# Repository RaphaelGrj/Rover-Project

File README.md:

# Rover-Project (Not Available - In development)
Coming soon

🤖 PROJECT ROVER | by R-Bot

L'évolution mobile de LUMI. 
Un compagnon robotique autonome, intelligent, et intégré à l'écosystème domotique, arborant la signature esthétique "Glitch" de R-Bot.

📖 Présentation du Projet 

Project Rover est le successeur spirituel de LUMI. Là où LUMI observait depuis son bureau, Rover explore. Fortement inspiré par la mécanique et l'expressivité du robot Vector (Anki), Rover va plus loin en devenant un véritable assistant domotique mobile.

Il ne s'agit pas d'un simple jouet télécommandé, mais d'une machine à émotions capable d'interagir naturellement avec son environnement et son humain. Conçu autour d'une architecture hybride (ESP32 WROOM embarqué + Raspberry Pi déporté sur le réseau), Rover surveille le logement, analyse l'air, interagit via une IA générative, et patrouille tout en gardant une direction artistique unique : un design "Vector Glitché".

🎯 Cahier des Charges & Fonctionnalités

  🧠 Machine à Émotions & IA
Personnalité Dynamique : Humeurs variables selon le contexte (météo, niveau de batterie, interactions récentes).
Expressivité Physique : Affichage d'animations sur écran IPS (yeux type Vector) combiné à des mouvements de tête fluides (Pitch/Yaw) gérés par servomoteurs.
Cerveau IA : Intégration d'une IA conversationnelle pour répondre aux requêtes de manière naturelle (évolution du système embarqué sur LUMI).
Mise en place d’un systeme de mise a jour OTA

  🛞 Mobilité & NavigationDéplacement Autonome : 
  Exploration libre du logement avec évitement d'obstacles.
  Pilotage Manuel : Prise de contrôle à distance via smartphone ou télécommande (avec retour vidéo direct).
  
  -[À l'étude] Cartographie & Patrouille : Algorithme SLAM pour générer une carte de la maison, avec des rondes de sécurité programmables.-
  -[À l'étude] Visualisation en réalité augmentée : la carte (et un premier HUD de télémétrie déjà en place) consultable en direct dans un casque compatible WebXR (ex. Meta Quest 3), en superposition sur la vraie pièce -- voir ARCHITECTURE_AND_ROADMAP.md §13.1.-
  
  👁️ Perception & VisionReconnaissance Visuelle : 
  Capacité à identifier son humain (reconnaissance faciale), à détecter des objets, des présences inconnues, ou même des animaux (idéal pour surveiller si votre compagnon fait des bêtises en votre absence).
  Surveillance Distante : Flux caméra accessible hors du domicile pour lever le doute lors d'une alerte.
  
  🏠 Hub Domotique & Capteurs (Home Assistant)
  Lien Home Assistant : Intégration native via MQTT/API. Rover peut déclencher des scènes ou annoncer des notifications de la maison.Bilan Météo Local : Station météo sur chenilles. 
  Analyse en temps réel de la température, de l'humidité et de la pression.
  -[À l'étude] Sécurité Environnementale : Détection de COV (Composés Organiques Volatils), de fumée et de qualité de l'air. Rover alerte en cas de risque d'incendie ou de dégradation de l'air intérieur.-
  
  🎨 Direction Artistique (DA)Design R-Bot "Glitch" : 
  Esthétique asymétrique, textures corrompues ou détails cyberpunk. Modélisation complète sous SolidWorks, optimisée pour un assemblage mêlant l'endurance du FDM (châssis) et la précision de la résine (coque/visage).
  
  ⚙️ Architecture Matérielle (BOM - Bill of Materials)
L'architecture est divisée en deux couches pour garantir fluidité et puissance de calcul.

### Cerveaux & Logique

| Composant | Rôle |
| :--- | :--- |
| **ESP32 WROOM** | *(embarqué)* Microcontrôleur temps réel : gestion des moteurs, servos, capteurs I2C et écran SPI. |
| **ESP32-CAM** | *(embarqué)* Module caméra indépendant, sert son flux MJPEG sur le réseau local. |
| **Raspberry Pi 3B+** | *(**déporté sur le réseau** depuis le 2026-09-15)* Serveur vidéo, traitement IA lourde, SLAM, lien Home Assistant. |

> **Le Raspberry Pi n'est plus embarqué sur le robot.** Il vit sur le
> réseau local et dialogue avec l'ESP32 par une socket TCP WiFi
> (Rover Protocol inchangé). Le châssis ne porte plus qu'ESP32 +
> ESP32-CAM + batterie --- gain d'encombrement et d'autonomie, et « le
> cerveau » peut désormais être n'importe quelle machine du LAN, pas
> forcément un Pi. Raisonnement complet :
> `ARCHITECTURE_AND_ROADMAP.md` §6.2.

### Locomotion & Mouvement

| Composant | Rôle |
| :--- | :--- |
| **2x Moteurs DC N20 (avec encodeurs)** | Propulsion précise des chenilles ou roues. |
| **1x Driver Moteur (DRV8833)** | Contrôle de puissance des moteurs. |
| **2x Micro Servomoteurs (SG90 ou MG90S)** | Mouvement de la tête (Axe X et Y) pour l'expressivité. |

### Perception & Capteurs

| Composant | Rôle |
| :--- | :--- |
| **Module Caméra (Pi Camera V2 ou OV2640)** | Vision, reconnaissance faciale, retour vidéo. |
| **MPU6050 (IMU)** | Accéléromètre & Gyroscope (équilibre, détection de chute ou si on le soulève). |
| **Capteur ToF (VL53L0X) x2** | Mesure de distance laser précise (évitement d'obstacles sans contact). |
| **BME688 (Bosch)** | Capteur 4-en-1 : Température, Humidité, Pression barométrique et Gaz/COV (idéal pour le bilan météo et risque incendie). |

### Interface Humain-Machine (IHM)

| Composant | Rôle |
| :--- | :--- |
| **Écran IPS (ex: ST7789 1.54")** | Affichage des yeux, des animations de glitch et des humeurs. |
| **Micro I2S (INMP441)** | Écoute de l'environnement et des commandes vocales. |
| **Ampli Audio (MAX98357A) + Haut-parleur** | Synthèse vocale et bruitages émotionnels. |

### Énergie

| Composant | Rôle |
| :--- | :--- |
| **2x Accus 18650 (Li-ion)** | Autonomie énergétique. |
| **Module BMS / TP4056 + Step-down (LM2596)** | Charge sécurisée et régulation 5V/3.3V pour alimenter l'ESP et le Pi. |

🚀 Roadmap du Développement (Prévisions)

[ ] Phase 1 : Preuve de concept (Châssis & Écran)

Conception SolidWorks de la base roulante.

Test de motorisation avec l'ESP32.

Portage des animations d'yeux depuis le projet LUMI.

[ ] Phase 2 : Architecture Hybride

Communication série/I2C entre le Pi Zero et l'ESP32-S3.

Intégration du flux vidéo et pilotage distant.

[ ] Phase 3 : Écosystème & IA

Connexion à Home Assistant.

Câblage et programmation des capteurs environnementaux (BME688).

Implémentation du modèle IA conversationnel.

[ ] Phase 4 : Les fonctions "À l'étude"

Déploiement d'un nœud ROS ou OpenCV pour le mode patrouille et le mapping.

Reconnaissance faciale et animale en local.

Projet développé par R-Bot. "Glitch the system, but make it cute."

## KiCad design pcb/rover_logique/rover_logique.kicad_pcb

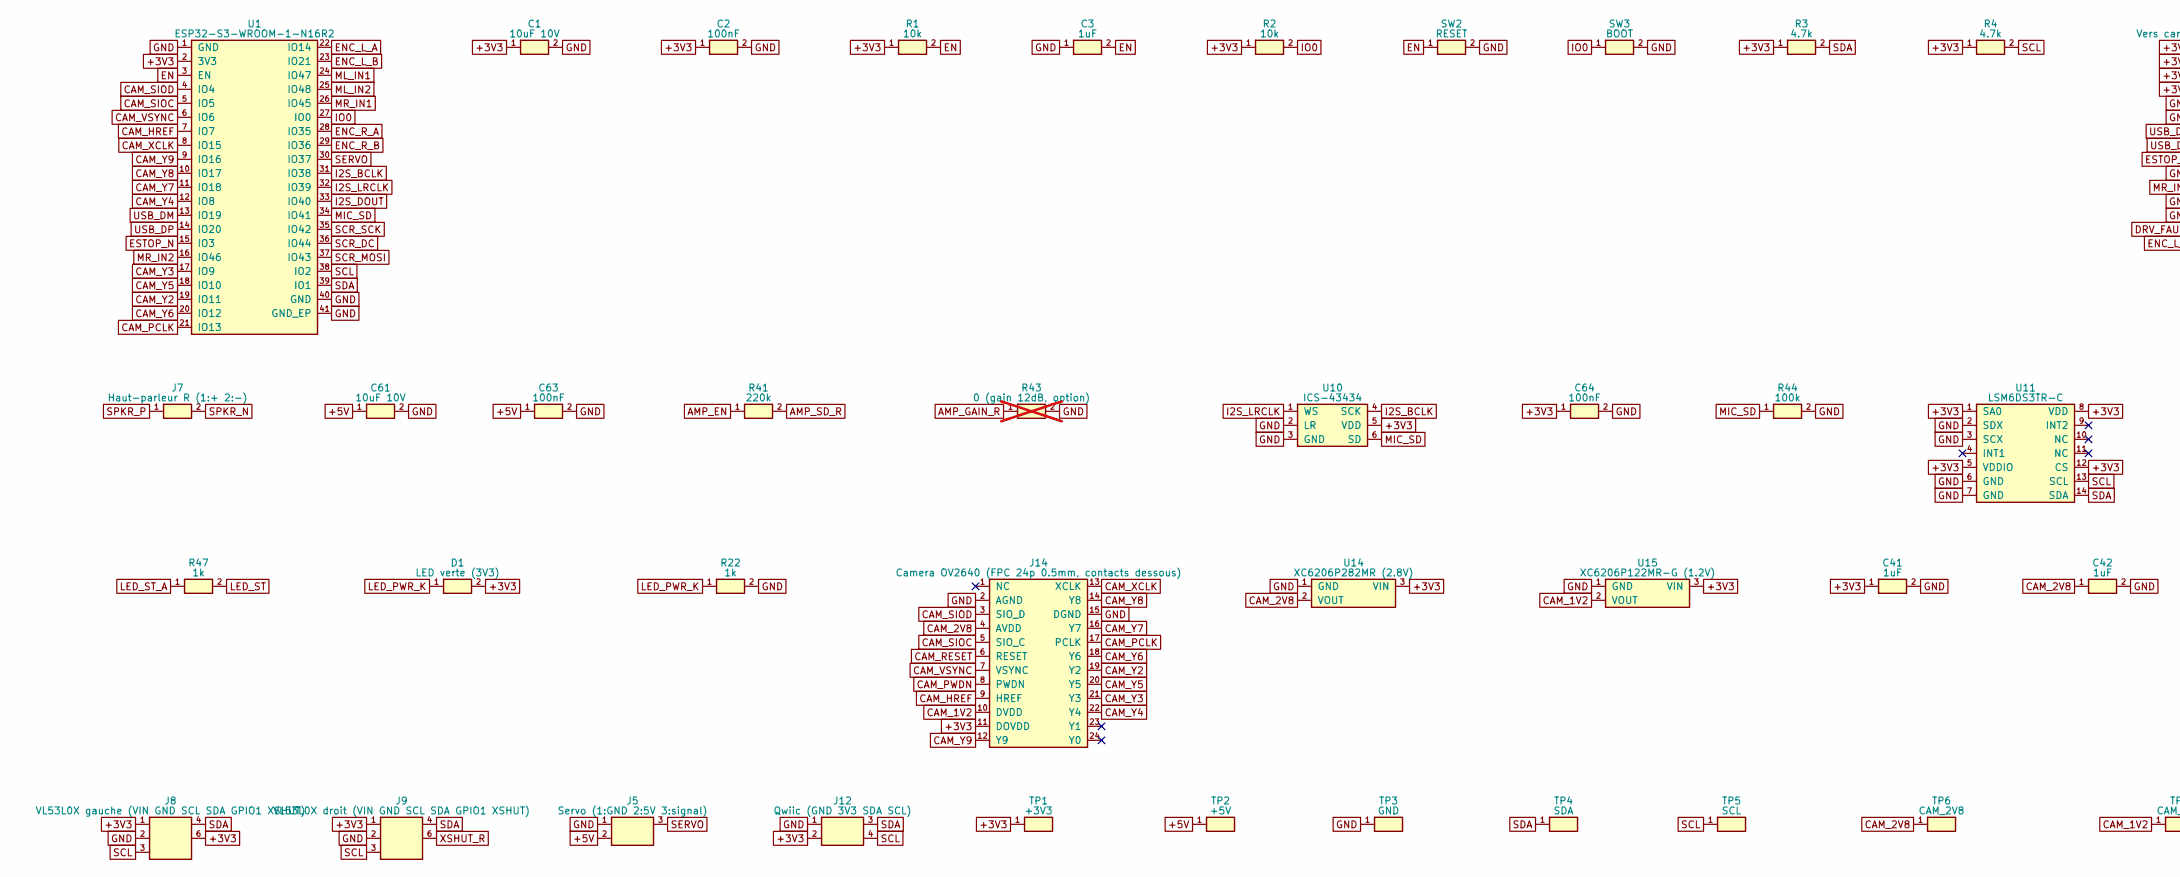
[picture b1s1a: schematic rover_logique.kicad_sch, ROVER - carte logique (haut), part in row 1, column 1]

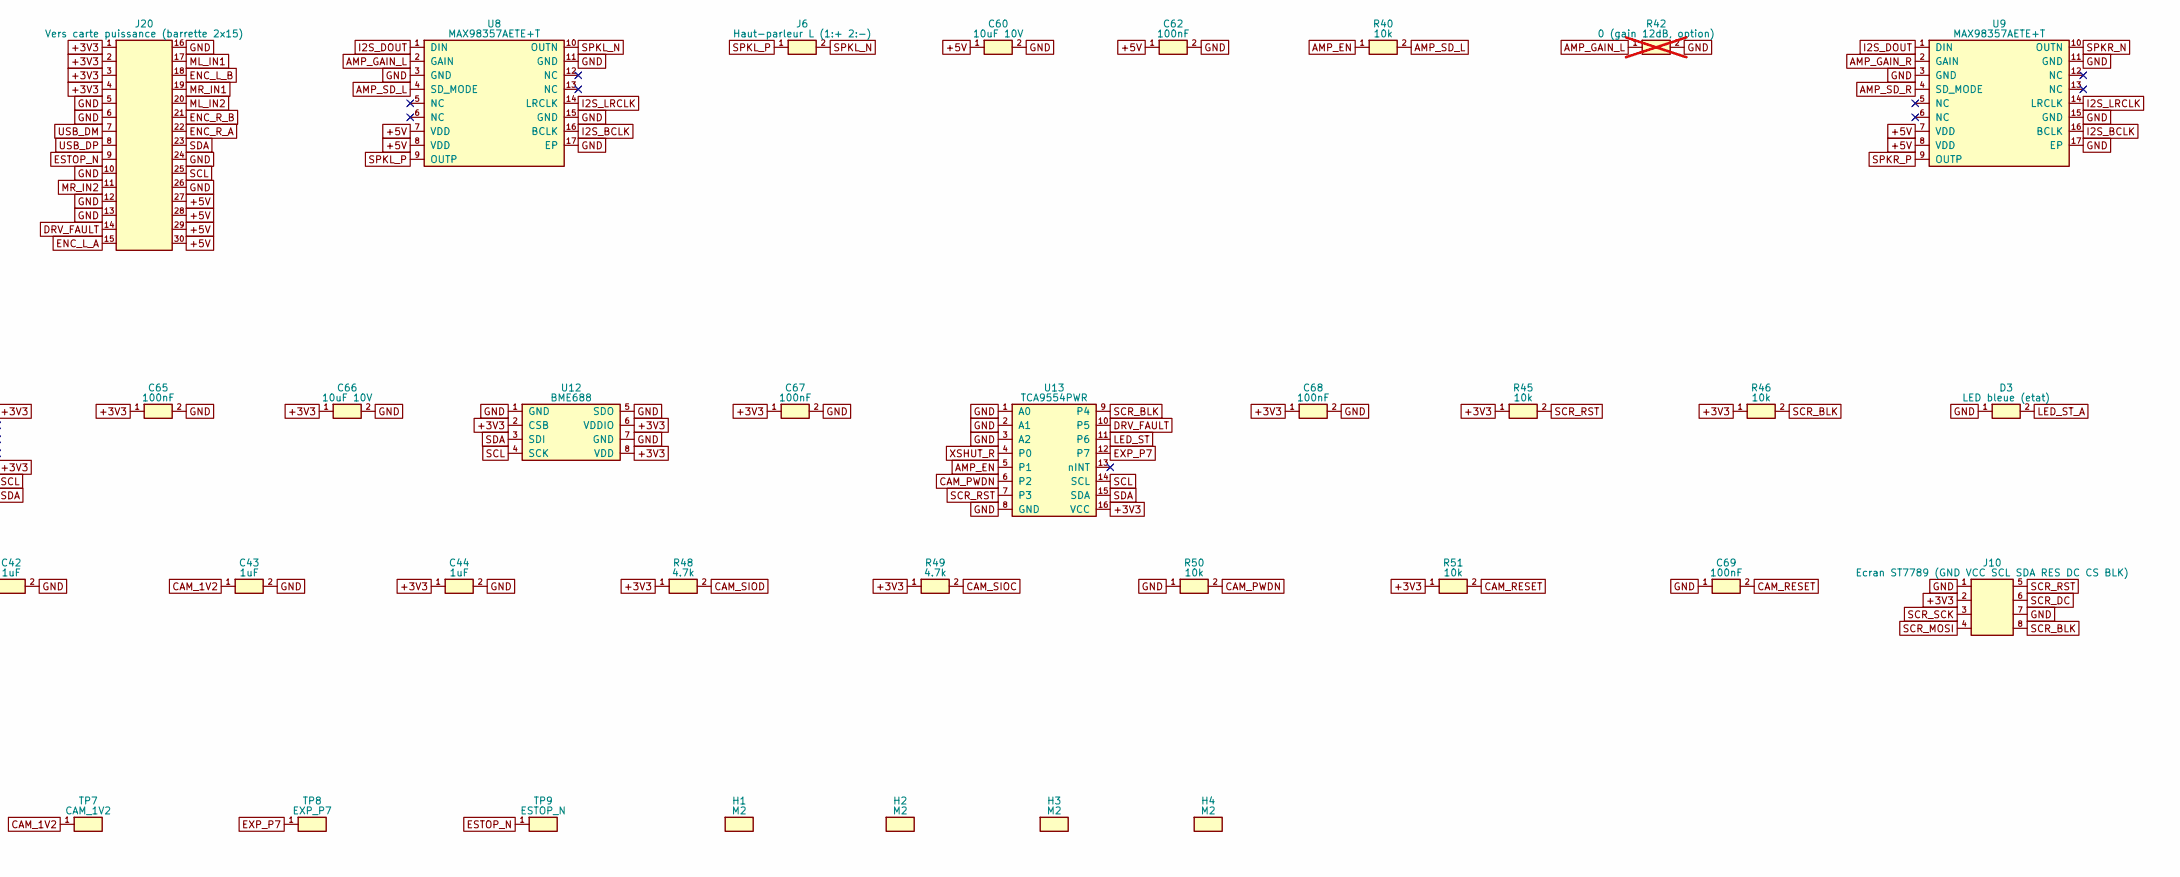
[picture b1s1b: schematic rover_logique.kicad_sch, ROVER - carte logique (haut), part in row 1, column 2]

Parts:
C1, C60, C61, C66: 10uF 10V; C_0805_2012Metric
C2, C62, C63, C64, C65, C67, C68, C69: 100nF; C_0402_1005Metric
C3, C41, C42, C43, C44: 1uF; C_0603_1608Metric
D1: LED verte (3V3); LED_0603_1608Metric
D3: LED bleue (etat); LED_0603_1608Metric
H1, H2, H3, H4: M2; MountingHole_2.2mm_M2
J5: Servo (1:GND 2:5V 3:signal); PinHeader_1x03_P2.54mm_Vertical
J6: Haut-parleur L (1:+ 2:-); JST_PH_S2B-PH-SM4-TB_1x02-1MP_P2.00mm_Horizontal
J7: Haut-parleur R (1:+ 2:-); JST_PH_S2B-PH-SM4-TB_1x02-1MP_P2.00mm_Horizontal
J8: VL53L0X gauche (VIN GND SCL SDA GPIO1 XSHUT); JST_PH_S6B-PH-SM4-TB_1x06-1MP_P2.00mm_Horizontal
J9: VL53L0X droit (VIN GND SCL SDA GPIO1 XSHUT); JST_PH_S6B-PH-SM4-TB_1x06-1MP_P2.00mm_Horizontal
J10: Ecran ST7789 (GND VCC SCL SDA RES DC CS BLK); JST_PH_S8B-PH-SM4-TB_1x08-1MP_P2.00mm_Horizontal
J12: Qwiic (GND 3V3 SDA SCL); JST_SH_SM04B-SRSS-TB_1x04-1MP_P1.00mm_Horizontal
J14: Camera OV2640 (FPC 24p 0.5mm, contacts dessous); Hirose_FH12-24S-0.5SH_1x24-1MP_P0.50mm_Horizontal
J20: Vers carte puissance (barrette 2x15); PinHeader_2x15_P2.54mm_Vertical
R1, R2, R40, R45, R46, R50, R51: 10k; R_0402_1005Metric
R3, R4, R48, R49: 4.7k; R_0402_1005Metric
R22, R47: 1k; R_0402_1005Metric
R41: 220k; R_0402_1005Metric
R42, R43: 0 (gain 12dB, option); R_0402_1005Metric; not fitted
R44: 100k; R_0402_1005Metric
SW2: RESET; SW_Push_1P1T_NO_CK_KMR2
SW3: BOOT; SW_Push_1P1T_NO_CK_KMR2
TP1: +3V3; TestPoint_Pad_D1.0mm
TP2: +5V; TestPoint_Pad_D1.0mm
TP3: GND; TestPoint_Pad_D1.0mm
TP4: SDA; TestPoint_Pad_D1.0mm
TP5: SCL; TestPoint_Pad_D1.0mm
TP6: CAM_2V8; TestPoint_Pad_D1.0mm
TP7: CAM_1V2; TestPoint_Pad_D1.0mm
TP8: EXP_P7; TestPoint_Pad_D1.0mm
TP9: ESTOP_N; TestPoint_Pad_D1.0mm
U1: ESP32-S3-WROOM-1-N16R2; ESP32-S3-WROOM-1_bord
U8, U9: MAX98357AETE+T; TQFN-16-1EP_3x3mm_P0.5mm_EP1.23x1.23mm
U10: ICS-43434; InvenSense_ICS-43434-6_3.5x2.65mm
U11: LSM6DS3TR-C; LGA-14_3x2.5mm_P0.5mm_LayoutBorder3x4y
U12: BME688; Bosch_LGA-8_3x3mm_P0.8mm_ClockwisePinNumbering
U13: TCA9554PWR; TSSOP-16_4.4x5mm_P0.65mm
U14: XC6206P282MR (2.8V); SOT-23
U15: XC6206P122MR-G (1.2V); SOT-23

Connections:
+3V3: C1.1, C2.1, C41.1, C44.1, C64.1, C65.1, C66.1, C67.1, C68.1, D1.2, J8.1, J8.6, J9.1, J10.2, J12.2, J14.11 (DOVDD), J20.1, J20.2, J20.3, J20.4, R1.1, R2.1, R3.1, R4.1, R45.1, R46.1, R48.1, R49.1, R51.1, TP1.1, U1.2 (3V3), U10.5 (VDD), U11.1 (SA0), U11.5 (VDDIO), U11.8 (VDD), U11.12 (CS), U12.2 (CSB), U12.6 (VDDIO), U12.8 (VDD), U13.16 (VCC), U14.3 (VIN), U15.3 (VIN)
+5V: C60.1, C61.1, C62.1, C63.1, J5.2, J20.27, J20.28, J20.29, J20.30, TP2.1, U8.7 (VDD), U8.8 (VDD), U9.7 (VDD), U9.8 (VDD)
AMP_EN: R40.1, R41.1, U13.5 (P1)
AMP_GAIN_L: R42.1, U8.2 (GAIN)
AMP_GAIN_R: R43.1, U9.2 (GAIN)
AMP_SD_L: R40.2, U8.4 (SD_MODE)
AMP_SD_R: R41.2, U9.4 (SD_MODE)
CAM_1V2: C43.1, J14.10 (DVDD), TP7.1, U15.2 (VOUT)
CAM_2V8: C42.1, J14.4 (AVDD), TP6.1, U14.2 (VOUT)
CAM_HREF: J14.9 (HREF), U1.7 (IO7)
CAM_PCLK: J14.17 (PCLK), U1.21 (IO13)
CAM_PWDN: J14.8 (PWDN), R50.2, U13.6 (P2)
CAM_RESET: C69.2, J14.6 (RESET), R51.2
CAM_SIOC: J14.5 (SIO_C), R49.2, U1.5 (IO5)
CAM_SIOD: J14.3 (SIO_D), R48.2, U1.4 (IO4)
CAM_VSYNC: J14.7 (VSYNC), U1.6 (IO6)
CAM_XCLK: J14.13 (XCLK), U1.8 (IO15)
CAM_Y2: J14.19 (Y2), U1.19 (IO11)
CAM_Y3: J14.21 (Y3), U1.17 (IO9)
CAM_Y4: J14.22 (Y4), U1.12 (IO8)
CAM_Y5: J14.20 (Y5), U1.18 (IO10)
CAM_Y6: J14.18 (Y6), U1.20 (IO12)
CAM_Y7: J14.16 (Y7), U1.11 (IO18)
CAM_Y8: J14.14 (Y8), U1.10 (IO17)
CAM_Y9: J14.12 (Y9), U1.9 (IO16)
DRV_FAULT: J20.14, U13.10 (P5)
EN: C3.2, R1.2, SW2.1, U1.3 (EN)
ENC_L_A: J20.15, U1.22 (IO14)
ENC_L_B: J20.18, U1.23 (IO21)
ENC_R_A: J20.22, U1.28 (IO35)
ENC_R_B: J20.21, U1.29 (IO36)
ESTOP_N: J20.9, TP9.1, U1.15 (IO3)
EXP_P7: TP8.1, U13.12 (P7)
GND: C1.2, C2.2, C3.1, C41.2, C42.2, C43.2, C44.2, C60.2, C61.2, C62.2, C63.2, C64.2, C65.2, C66.2, C67.2, C68.2, C69.1, D3.1, J5.1, J8.2, J9.2, J10.1, J10.7, J12.1, J14.2 (AGND), J14.15 (DGND), J20.5, J20.6, J20.10, J20.12, J20.13, J20.16, J20.24, J20.26, R22.2, R42.2, R43.2, R44.2, R50.1, SW2.2, SW3.2, TP3.1, U1.1 (GND), U1.40 (GND), U1.41 (GND_EP), U8.3 (GND), U8.11 (GND), U8.15 (GND), U8.17 (EP), U9.3 (GND), U9.11 (GND), U9.15 (GND), U9.17 (EP), U10.2 (LR), U10.3 (GND), U11.2 (SDX), U11.3 (SCX), U11.6 (GND), U11.7 (GND), U12.1 (GND), U12.5 (SDO), U12.7 (GND), U13.1 (A0), U13.2 (A1), U13.3 (A2), U13.8 (GND), U14.1 (GND), U15.1 (GND)
I2S_BCLK: U1.31 (IO38), U8.16 (BCLK), U9.16 (BCLK), U10.4 (SCK)
I2S_DOUT: U1.33 (IO40), U8.1 (DIN), U9.1 (DIN)
I2S_LRCLK: U1.32 (IO39), U8.14 (LRCLK), U9.14 (LRCLK), U10.1 (WS)
IO0: R2.2, SW3.1, U1.27 (IO0)
LED_PWR_K: D1.1, R22.1
LED_ST: R47.2, U13.11 (P6)
LED_ST_A: D3.2, R47.1
MIC_SD: R44.1, U1.34 (IO41), U10.6 (SD)
ML_IN1: J20.17, U1.24 (IO47)
ML_IN2: J20.20, U1.25 (IO48)
MR_IN1: J20.19, U1.26 (IO45)
MR_IN2: J20.11, U1.16 (IO46)
SCL: J8.3, J9.3, J12.4, J20.25, R4.2, TP5.1, U1.38 (IO2), U11.13 (SCL), U12.4 (SCK), U13.14 (SCL)
SCR_BLK: J10.8, R46.2, U13.9 (P4)
SCR_DC: J10.6, U1.36 (IO44)
SCR_MOSI: J10.4, U1.37 (IO43)
SCR_RST: J10.5, R45.2, U13.7 (P3)
SCR_SCK: J10.3, U1.35 (IO42)
SDA: J8.4, J9.4, J12.3, J20.23, R3.2, TP4.1, U1.39 (IO1), U11.14 (SDA), U12.3 (SDI), U13.15 (SDA)
SERVO: J5.3, U1.30 (IO37)
SPKL_N: J6.2, U8.10 (OUTN)
SPKL_P: J6.1, U8.9 (OUTP)
SPKR_N: J7.2, U9.10 (OUTN)
SPKR_P: J7.1, U9.9 (OUTP)
USB_DM: J20.7, U1.13 (IO19)
USB_DP: J20.8, U1.14 (IO20)
XSHUT_R: J9.6, U13.4 (P0)

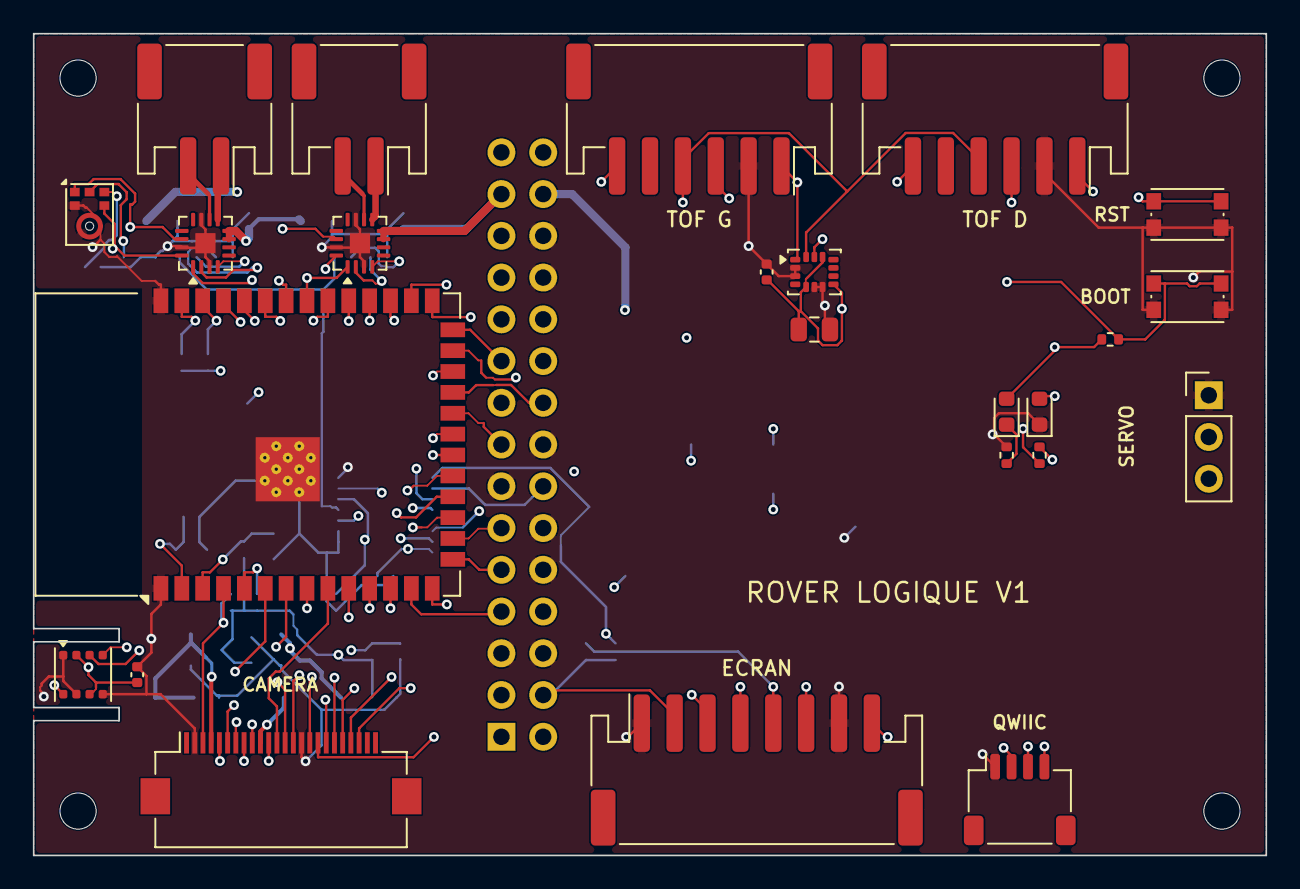
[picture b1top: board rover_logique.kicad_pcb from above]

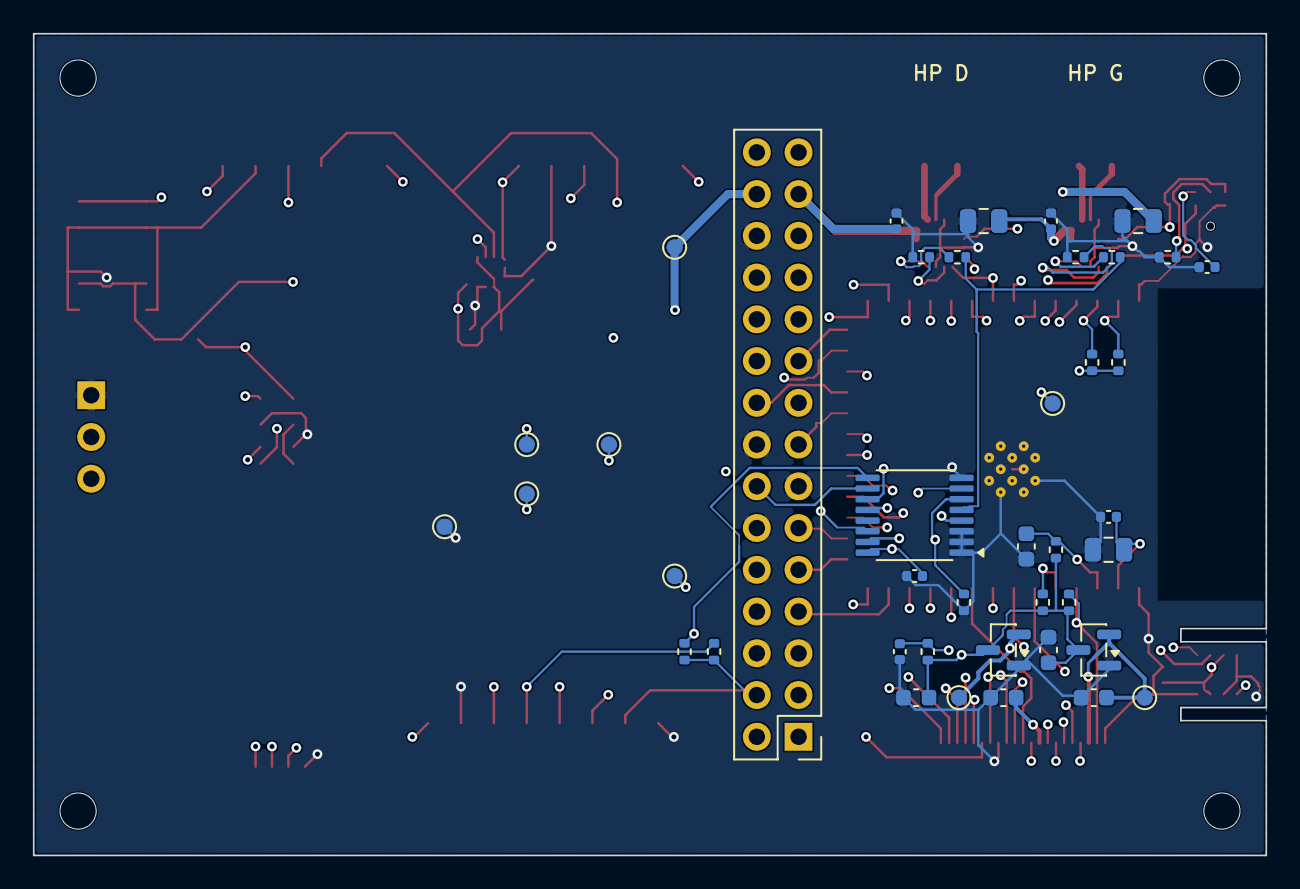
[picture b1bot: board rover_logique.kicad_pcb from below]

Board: 4 copper layers, 75.0 x 50.0 mm, 69 parts (41 on the bottom side), 61 nets.

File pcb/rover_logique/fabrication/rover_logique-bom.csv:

Comment,Designator,Footprint,LCSC Part #
10uF 10V,"C1,C60,C61,C66",C_0805_2012Metric,
100nF,"C2,C62,C63,C64,C65,C67,C68,C69",C_0402_1005Metric,
1uF,"C3,C41,C42,C43,C44",C_0603_1608Metric,
LED verte (3V3),D1,LED_0603_1608Metric,
LED bleue (etat),D3,LED_0603_1608Metric,
Ecran ST7789 (GND VCC SCL SDA RES DC CS BLK),J10,JST_PH_S8B-PH-SM4-TB_1x08-1MP_P2.00mm_Horizontal,C265121
Qwiic (GND 3V3 SDA SCL),J12,JST_SH_SM04B-SRSS-TB_1x04-1MP_P1.00mm_Horizontal,C160404
"Camera OV2640 (FPC 24p 0.5mm, contacts dessous)",J14,Hirose_FH12-24S-0.5SH_1x24-1MP_P0.50mm_Horizontal,
Vers carte puissance (barrette 2x15),J20,PinHeader_2x15_P2.54mm_Vertical,
Servo (1:GND 2:5V 3:signal),J5,PinHeader_1x03_P2.54mm_Vertical,
Haut-parleur L (1:+ 2:-),J6,JST_PH_S2B-PH-SM4-TB_1x02-1MP_P2.00mm_Horizontal,C295747
Haut-parleur R (1:+ 2:-),J7,JST_PH_S2B-PH-SM4-TB_1x02-1MP_P2.00mm_Horizontal,C295747
VL53L0X gauche (VIN GND SCL SDA GPIO1 XSHUT),J8,JST_PH_S6B-PH-SM4-TB_1x06-1MP_P2.00mm_Horizontal,C265405
VL53L0X droit (VIN GND SCL SDA GPIO1 XSHUT),J9,JST_PH_S6B-PH-SM4-TB_1x06-1MP_P2.00mm_Horizontal,C265405
10k,"R1,R2,R40,R45,R46,R50,R51",R_0402_1005Metric,
4.7k,"R3,R4,R48,R49",R_0402_1005Metric,
220k,R41,R_0402_1005Metric,
100k,R44,R_0402_1005Metric,
1k,"R47,R22",R_0402_1005Metric,
RESET,SW2,SW_Push_1P1T_NO_CK_KMR2,
BOOT,SW3,SW_Push_1P1T_NO_CK_KMR2,
ESP32-S3-WROOM-1-N16R2,U1,ESP32-S3-WROOM-1_bord,C2913205
ICS-43434,U10,InvenSense_ICS-43434-6_3.5x2.65mm,C5656610
LSM6DS3TR-C,U11,LGA-14_3x2.5mm_P0.5mm_LayoutBorder3x4y,C967633
BME688,U12,Bosch_LGA-8_3x3mm_P0.8mm_ClockwisePinNumbering,C3664478
TCA9554PWR,U13,TSSOP-16_4.4x5mm_P0.65mm,C477924
XC6206P282MR (2.8V),U14,SOT-23,C347374
XC6206P122MR-G (1.2V),U15,SOT-23,C424699
MAX98357AETE+T,"U8,U9",TQFN-16-1EP_3x3mm_P0.5mm_EP1.23x1.23mm,C910544

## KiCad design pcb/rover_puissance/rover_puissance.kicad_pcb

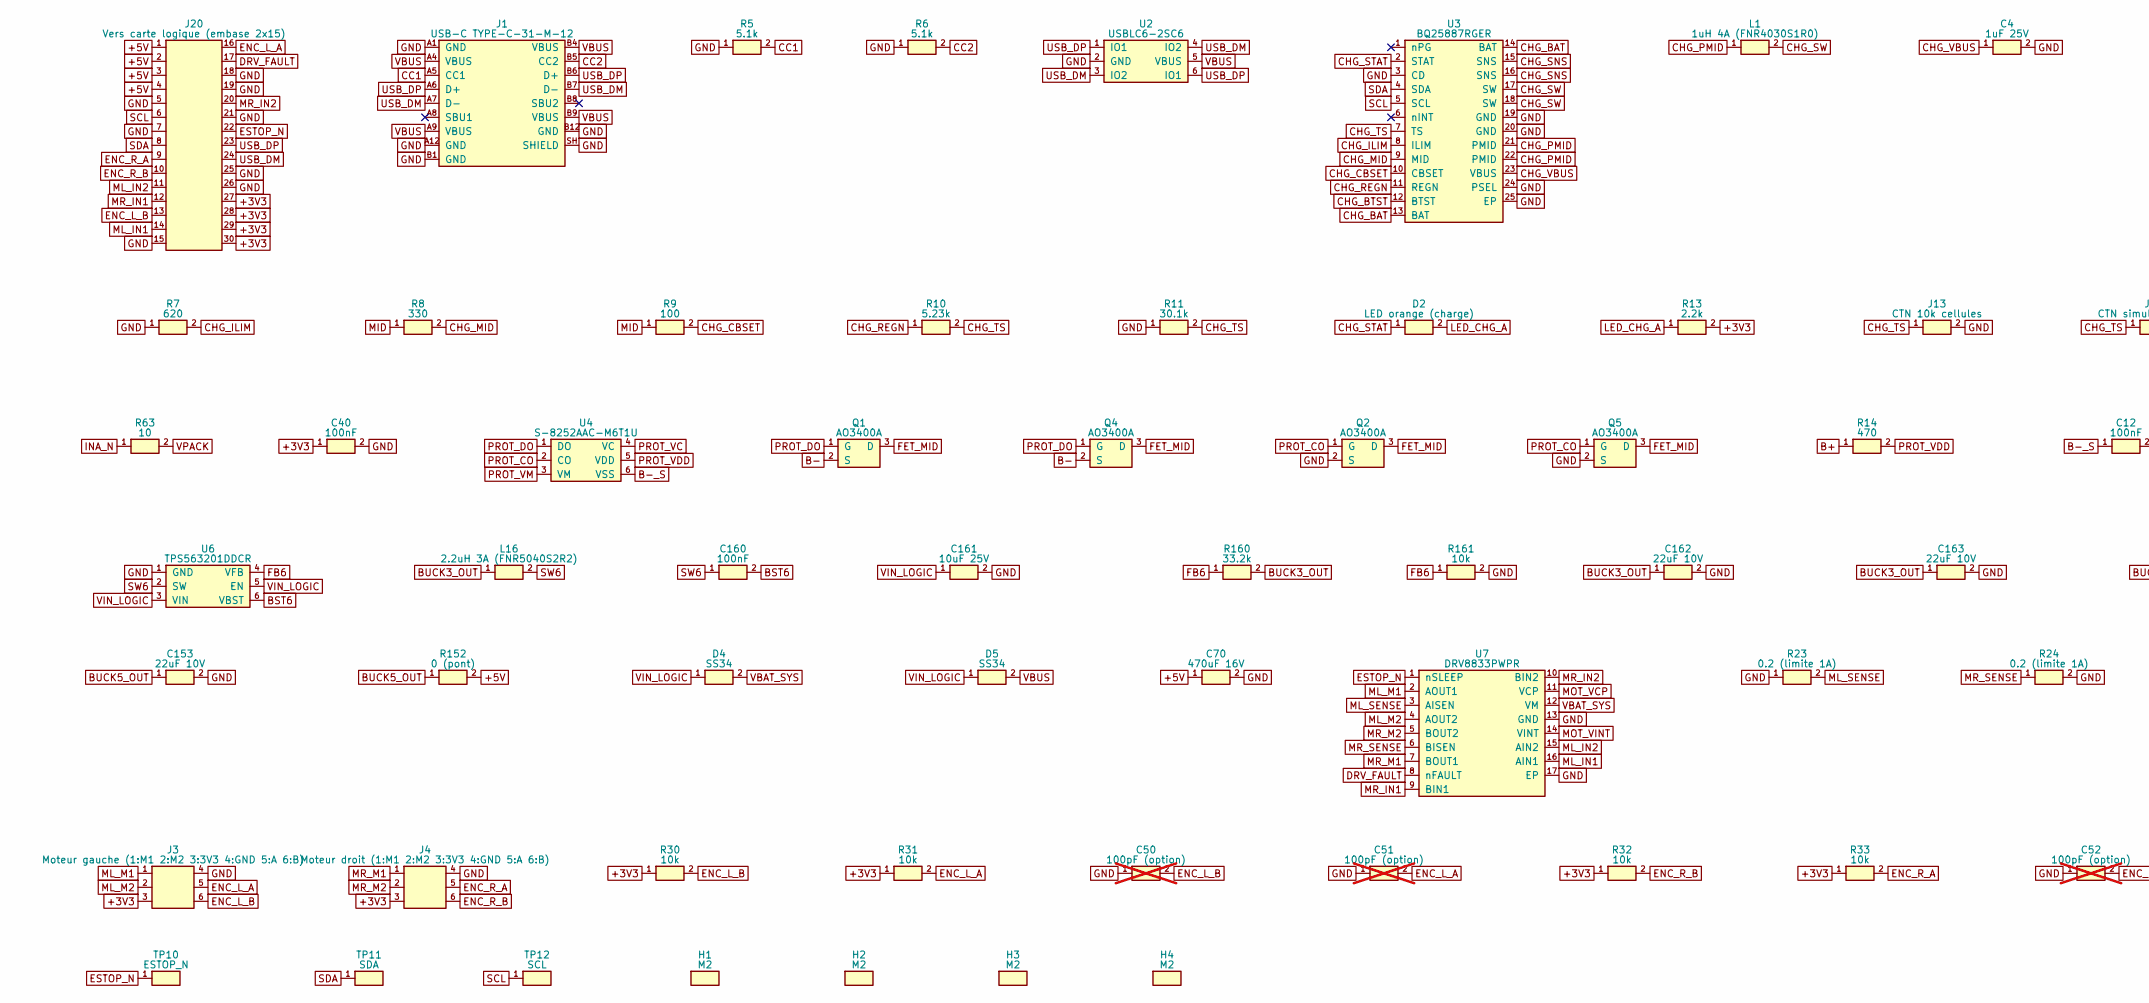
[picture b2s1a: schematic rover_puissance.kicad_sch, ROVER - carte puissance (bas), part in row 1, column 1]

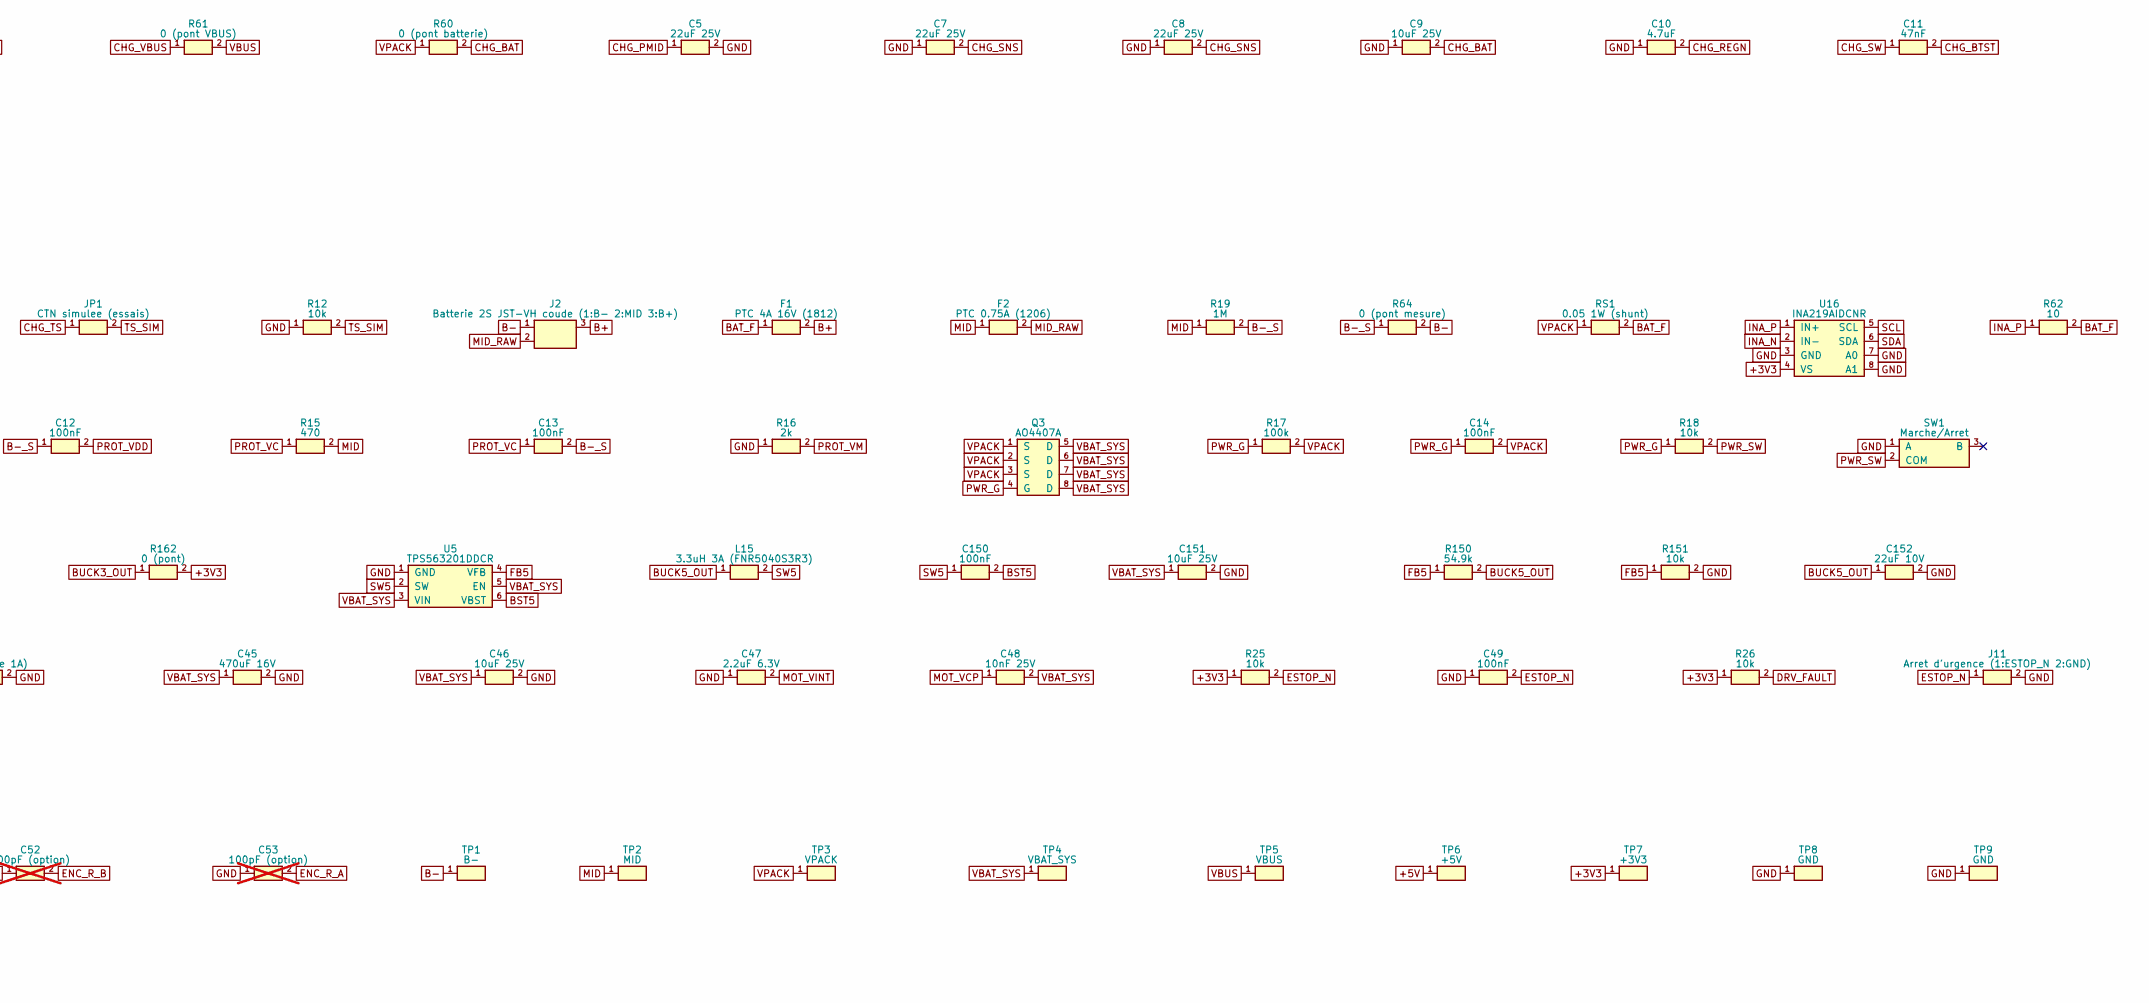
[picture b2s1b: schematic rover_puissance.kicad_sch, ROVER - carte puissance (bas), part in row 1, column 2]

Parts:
C4: 1uF 25V; C_0603_1608Metric
C5, C7, C8: 22uF 25V; C_0805_2012Metric
C9, C46, C151, C161: 10uF 25V; C_0805_2012Metric
C10: 4.7uF; C_0603_1608Metric
C11: 47nF; C_0402_1005Metric
C12, C13, C14, C40, C49, C150, C160: 100nF; C_0402_1005Metric
C45, C70: 470uF 16V; CP_Elec_8x10
C47: 2.2uF 6.3V; C_0402_1005Metric
C48: 10nF 25V; C_0402_1005Metric
C50, C51, C52, C53: 100pF (option); C_0402_1005Metric; not fitted
C152, C153, C162, C163: 22uF 10V; C_0805_2012Metric
D2: LED orange (charge); LED_0603_1608Metric
D4, D5: SS34; D_SMA
F1: PTC 4A 16V (1812); Fuse_1812_4532Metric
F2: PTC 0.75A (1206); Fuse_1206_3216Metric
H1, H2, H3, H4: M2; MountingHole_2.2mm_M2
J1: USB-C TYPE-C-31-M-12; USB_C_Receptacle_HRO_TYPE-C-31-M-12
J2: Batterie 2S JST-VH coude (1:B- 2:MID 3:B+); JST_VH_B3PS-VH_1x03_P3.96mm_Horizontal
J3: Moteur gauche (1:M1 2:M2 3:3V3 4:GND 5:A 6:B); JST_PH_S6B-PH-SM4-TB_1x06-1MP_P2.00mm_Horizontal
J4: Moteur droit (1:M1 2:M2 3:3V3 4:GND 5:A 6:B); JST_PH_S6B-PH-SM4-TB_1x06-1MP_P2.00mm_Horizontal
J11: Arret d'urgence (1:ESTOP_N 2:GND); JST_PH_S2B-PH-SM4-TB_1x02-1MP_P2.00mm_Horizontal
J13: CTN 10k cellules; JST_PH_S2B-PH-SM4-TB_1x02-1MP_P2.00mm_Horizontal
J20: Vers carte logique (embase 2x15); PinSocket_2x15_P2.54mm_Vertical
JP1: CTN simulee (essais); SolderJumper-2_P1.3mm_Open_RoundedPad1.0x1.5mm
L1: 1uH 4A (FNR4030S1R0); L_Changjiang_FNR4030S
L15: 3.3uH 3A (FNR5040S3R3); L_Changjiang_FNR5040S
L16: 2.2uH 3A (FNR5040S2R2); L_Changjiang_FNR5040S
Q1, Q2, Q4, Q5: AO3400A; SOT-23
Q3: AO4407A; SOIC-8_3.9x4.9mm_P1.27mm
R5, R6: 5.1k; R_0402_1005Metric
R7: 620; R_0402_1005Metric
R8: 330; R_0402_1005Metric
R9: 100; R_1206_3216Metric
R10: 5.23k; R_0402_1005Metric
R11: 30.1k; R_0402_1005Metric
R12, R18, R25, R26, R30, R31, R32, R33, R151, R161: 10k; R_0402_1005Metric
R13: 2.2k; R_0402_1005Metric
R14, R15: 470; R_0402_1005Metric
R16: 2k; R_0402_1005Metric
R17: 100k; R_0402_1005Metric
R19: 1M; R_0402_1005Metric
R23, R24: 0.2 (limite 1A); R_1206_3216Metric
R60: 0 (pont batterie); R_1206_3216Metric
R61: 0 (pont VBUS); R_1206_3216Metric
R62, R63: 10; R_0402_1005Metric
R64: 0 (pont mesure); R_0402_1005Metric
R150: 54.9k; R_0402_1005Metric
R152, R162: 0 (pont); R_1206_3216Metric
R160: 33.2k; R_0402_1005Metric
RS1: 0.05 1W (shunt); R_2512_6332Metric
SW1: Marche/Arret; SW_SPDT_PCM12
TP1: B-; TestPoint_Pad_D1.0mm
TP2: MID; TestPoint_Pad_D1.0mm
TP3: VPACK; TestPoint_Pad_D1.0mm
TP4: VBAT_SYS; TestPoint_Pad_D1.0mm
TP5: VBUS; TestPoint_Pad_D1.0mm
TP6: +5V; TestPoint_Pad_D1.0mm
TP7: +3V3; TestPoint_Pad_D1.0mm
TP8, TP9: GND; TestPoint_Pad_D1.0mm
TP10: ESTOP_N; TestPoint_Pad_D1.0mm
TP11: SDA; TestPoint_Pad_D1.0mm
TP12: SCL; TestPoint_Pad_D1.0mm
U2: USBLC6-2SC6; SOT-23-6
U3: BQ25887RGER; Texas_RGE0024H_VQFN-24-1EP_4x4mm_P0.5mm_EP2.7x2.7mm
U4: S-8252AAC-M6T1U; SOT-23-6
U5, U6: TPS563201DDCR; SOT-23-6
U7: DRV8833PWPR; HTSSOP-16-1EP_4.4x5mm_P0.65mm_EP3.4x5mm
U16: INA219AIDCNR; SOT-23-8

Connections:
+3V3: C40.1, J3.3, J4.3, J20.27, J20.28, J20.29, J20.30, R13.2, R25.1, R26.1, R30.1, R31.1, R32.1, R33.1, R162.2, TP7.1, U16.4 (VS)
+5V: C70.1, J20.1, J20.2, J20.3, J20.4, R152.2, TP6.1
B+: F1.2, J2.3, R14.1
B-: J2.1, Q1.2 (S), Q4.2 (S), R64.2, TP1.1
B-_S: C12.1, C13.2, R19.2, R64.1, U4.6 (VSS)
BAT_F: F1.1, R62.2, RS1.2
BST5: C150.2, U5.6 (VBST)
BST6: C160.2, U6.6 (VBST)
BUCK3_OUT: C162.1, C163.1, L16.1, R160.2, R162.1
BUCK5_OUT: C152.1, C153.1, L15.1, R150.2, R152.1
CC1: J1.A5 (CC1), R5.2
CC2: J1.B5 (CC2), R6.2
CHG_BAT: C9.2, R60.2, U3.13 (BAT), U3.14 (BAT)
CHG_BTST: C11.2, U3.12 (BTST)
CHG_CBSET: R9.2, U3.10 (CBSET)
CHG_ILIM: R7.2, U3.8 (ILIM)
CHG_MID: R8.2, U3.9 (MID)
CHG_PMID: C5.1, L1.1, U3.21 (PMID), U3.22 (PMID)
CHG_REGN: C10.2, R10.1, U3.11 (REGN)
CHG_SNS: C7.2, C8.2, U3.15 (SNS), U3.16 (SNS)
CHG_STAT: D2.1, U3.2 (STAT)
CHG_SW: C11.1, L1.2, U3.17 (SW), U3.18 (SW)
CHG_TS: J13.1, JP1.1, R10.2, R11.2, U3.7 (TS)
CHG_VBUS: C4.1, R61.1, U3.23 (VBUS)
DRV_FAULT: J20.17, R26.2, U7.8 (nFAULT)
ENC_L_A: C51.2, J3.5, J20.16, R31.2
ENC_L_B: C50.2, J3.6, J20.13, R30.2
ENC_R_A: C53.2, J4.5, J20.9, R33.2
ENC_R_B: C52.2, J4.6, J20.10, R32.2
ESTOP_N: C49.2, J11.1, J20.22, R25.2, TP10.1, U7.1 (nSLEEP)
FB5: R150.1, R151.1, U5.4 (VFB)
FB6: R160.1, R161.1, U6.4 (VFB)
FET_MID: Q1.3 (D), Q2.3 (D), Q4.3 (D), Q5.3 (D)
GND: C4.2, C5.2, C7.1, C8.1, C9.1, C10.1, C40.2, C45.2, C46.2, C47.1, C49.1, C50.1, C51.1, C52.1, C53.1, C70.2, C151.2, C152.2, C153.2, C161.2, C162.2, C163.2, J1.A1 (GND), J1.A12 (GND), J1.B1 (GND), J1.B12 (GND), J1.SH (SHIELD), J3.4, J4.4, J11.2, J13.2, J20.5, J20.7, J20.15, J20.18, J20.19, J20.21, J20.25, J20.26, Q2.2 (S), Q5.2 (S), R5.1, R6.1, R7.1, R11.1, R12.1, R16.1, R23.1, R24.2, R151.2, R161.2, SW1.1 (A), TP8.1, TP9.1, U2.2 (GND), U3.3 (CD), U3.19 (GND), U3.20 (GND), U3.24 (PSEL), U3.25 (EP), U5.1 (GND), U6.1 (GND), U7.13 (GND), U7.17 (EP), U16.3 (GND), U16.7 (A0), U16.8 (A1)
INA_N: R63.1, U16.2 (IN-)
INA_P: R62.1, U16.1 (IN+)
LED_CHG_A: D2.2, R13.1
MID: F2.1, R8.1, R9.1, R15.2, R19.1, TP2.1
MID_RAW: F2.2, J2.2
ML_IN1: J20.14, U7.16 (AIN1)
ML_IN2: J20.11, U7.15 (AIN2)
ML_M1: J3.1, U7.2 (AOUT1)
ML_M2: J3.2, U7.4 (AOUT2)
ML_SENSE: R23.2, U7.3 (AISEN)
MOT_VCP: C48.1, U7.11 (VCP)
MOT_VINT: C47.2, U7.14 (VINT)
MR_IN1: J20.12, U7.9 (BIN1)
MR_IN2: J20.20, U7.10 (BIN2)
MR_M1: J4.1, U7.7 (BOUT1)
MR_M2: J4.2, U7.5 (BOUT2)
MR_SENSE: R24.1, U7.6 (BISEN)
PROT_CO: Q2.1 (G), Q5.1 (G), U4.2 (CO)
PROT_DO: Q1.1 (G), Q4.1 (G), U4.1 (DO)
PROT_VC: C13.1, R15.1, U4.4 (VC)
PROT_VDD: C12.2, R14.2, U4.5 (VDD)
PROT_VM: R16.2, U4.3 (VM)
PWR_G: C14.1, Q3.4 (G), R17.1, R18.1
PWR_SW: R18.2, SW1.2 (COM)
SCL: J20.6, TP12.1, U3.5 (SCL), U16.5 (SCL)
SDA: J20.8, TP11.1, U3.4 (SDA), U16.6 (SDA)
SW5: C150.1, L15.2, U5.2 (SW)
SW6: C160.1, L16.2, U6.2 (SW)
TS_SIM: JP1.2, R12.2
USB_DM: J1.A7 (D-), J1.B7 (D-), J20.24, U2.3 (IO2), U2.4 (IO2)
USB_DP: J1.A6 (D+), J1.B6 (D+), J20.23, U2.1 (IO1), U2.6 (IO1)
VBAT_SYS: C45.1, C46.1, C48.2, C151.1, D4.2, Q3.5 (D), Q3.6 (D), Q3.7 (D), Q3.8 (D), TP4.1, U5.3 (VIN), U5.5 (EN), U7.12 (VM)
VBUS: D5.2, J1.A4 (VBUS), J1.A9 (VBUS), J1.B4 (VBUS), J1.B9 (VBUS), R61.2, TP5.1, U2.5 (VBUS)
VIN_LOGIC: C161.1, D4.1, D5.1, U6.3 (VIN), U6.5 (EN)
VPACK: C14.2, Q3.1 (S), Q3.2 (S), Q3.3 (S), R17.2, R60.1, R63.2, RS1.1, TP3.1
